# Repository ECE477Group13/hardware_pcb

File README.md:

# hardware_pcb
GitHub backup of PCB design files (Schematic and Board files)

here is a test change.

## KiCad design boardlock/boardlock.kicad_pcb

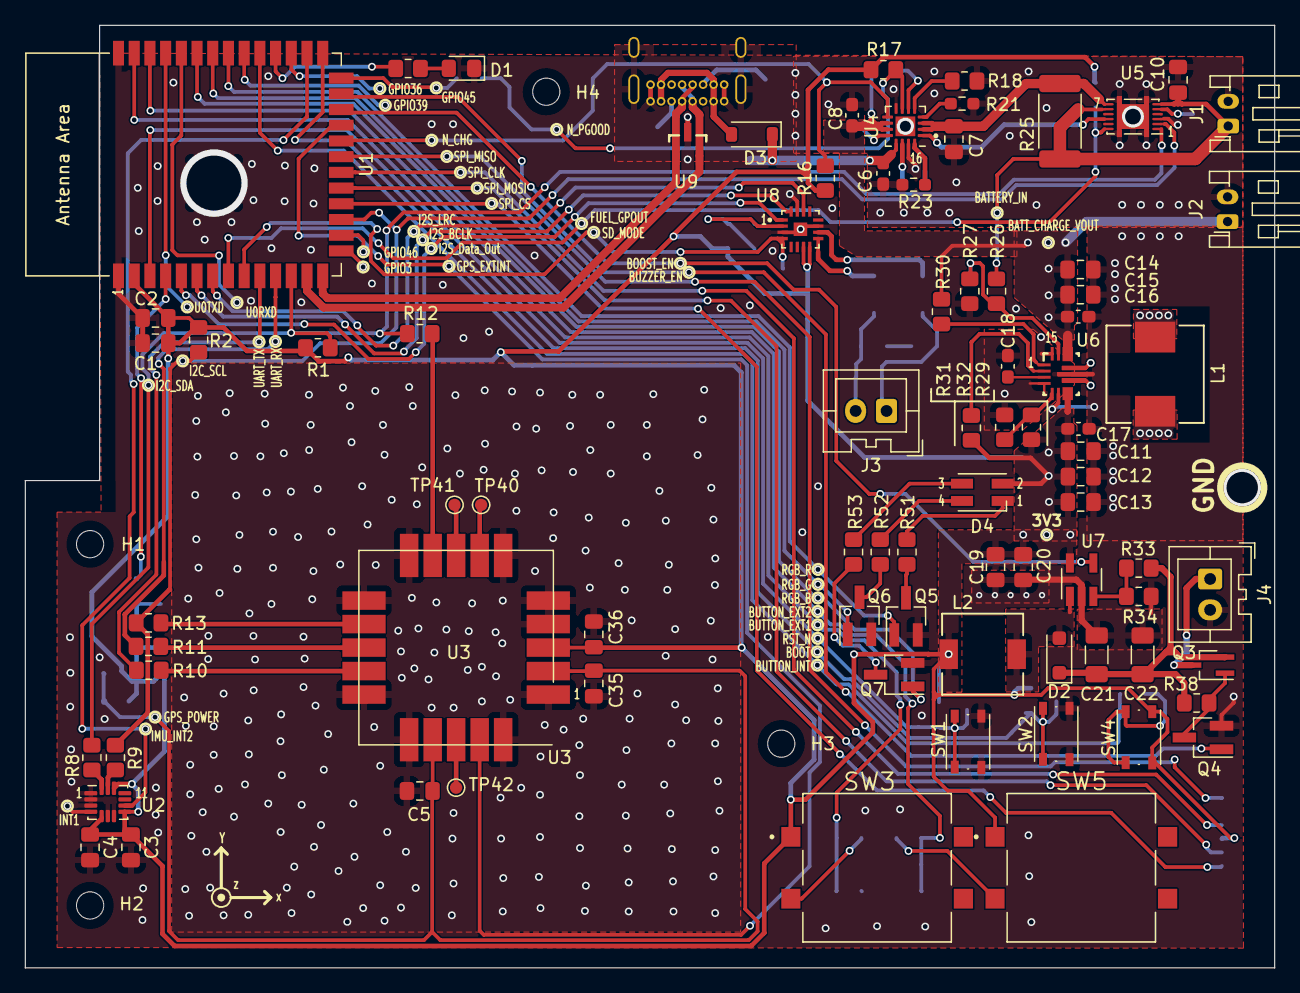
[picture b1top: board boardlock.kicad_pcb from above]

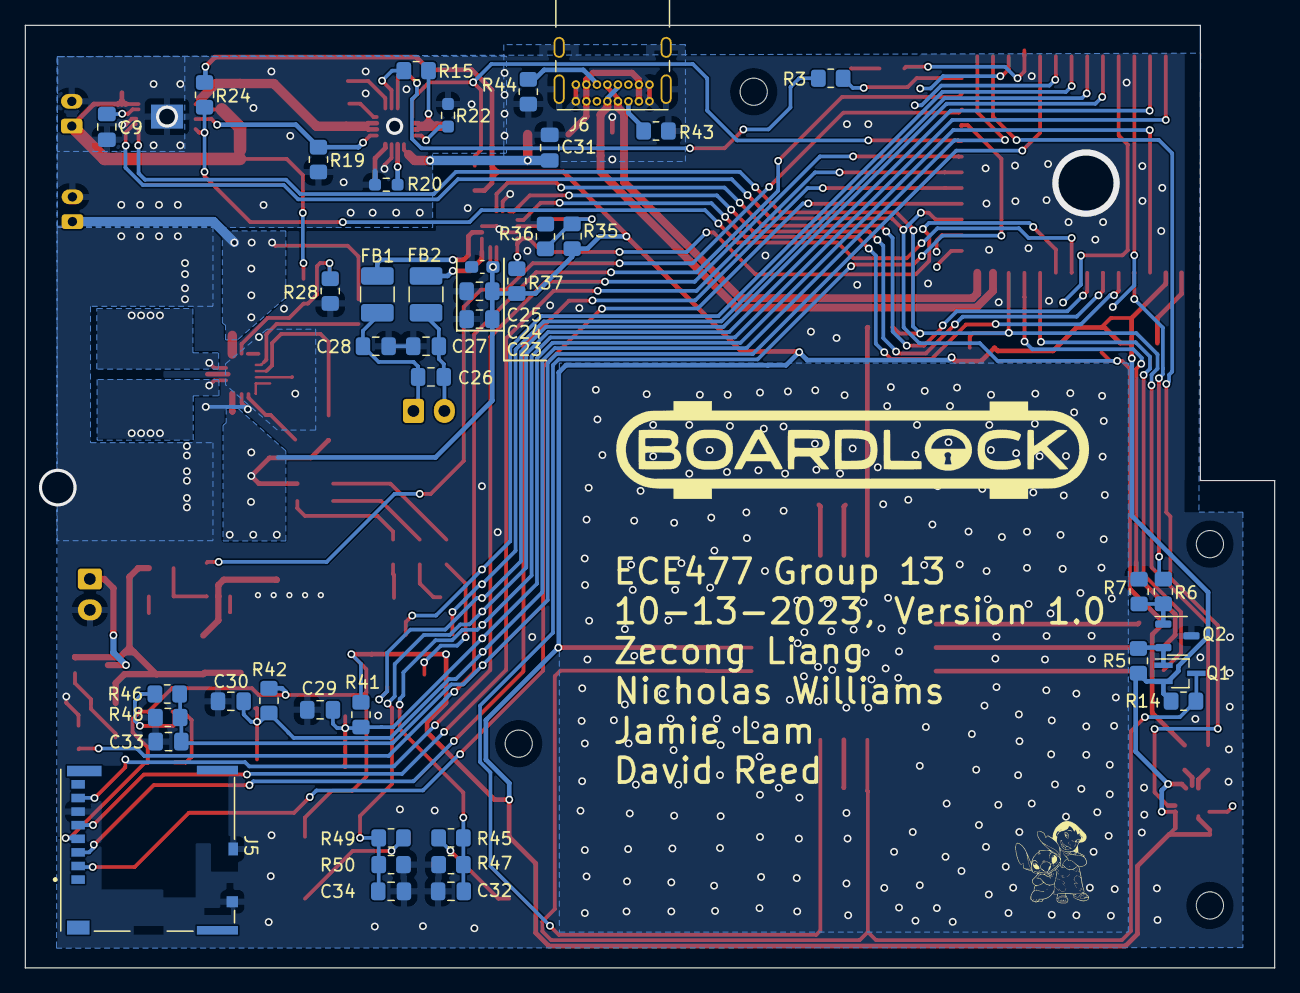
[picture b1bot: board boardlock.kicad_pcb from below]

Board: 2 copper layers, 101.0 x 76.2 mm, 129 parts (43 on the bottom side), 88 nets.

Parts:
C1, C7, C19, C20, C23, C24, C31: 10uF; C_0805_2012Metric_Pad1.18x1.45mm_HandSolder
C2, C29, C30, C32, C33, C34: 0.1uF; C_0805_2012Metric_Pad1.18x1.45mm_HandSolder
C3, C4: 100nF; C_0805_2012Metric_Pad1.18x1.45mm_HandSolder
C5, C35, C36: 1.0uF; C_0805_2012Metric_Pad1.18x1.45mm_HandSolder
C6: 1uF; C_0603_1608Metric_Pad1.08x0.95mm_HandSolder
C8, C16, C17: 10uF; C_0603_1608Metric_Pad1.08x0.95mm_HandSolder
C9: 0.47uF; C_0805_2012Metric_Pad1.18x1.45mm_HandSolder
C10: 1uF; C_0805_2012Metric_Pad1.18x1.45mm_HandSolder
C11, C12, C13, C14, C15: 22uF; C_0805_2012Metric_Pad1.18x1.45mm_HandSolder
C18: 100nF; C_0603_1608Metric_Pad1.08x0.95mm_HandSolder
C21, C22: 10uF; C_1206_3216Metric_Pad1.33x1.80mm_HandSolder
C25: 0.1uF; C_0603_1608Metric_Pad1.08x0.95mm_HandSolder
C26, C27, C28: 47n; C_0805_2012Metric_Pad1.18x1.45mm_HandSolder
D1: LED; LED_0805_2012Metric_Pad1.15x1.40mm_HandSolder
D2: PMEG2005EH; D_SOD-123F
D3: 1N5819HW1-7-F; D_SOD-123
D4: CLVBA-FKA-CC1F1L1BB7R3R3D; LED_Cree-PLCC4_3.2x2.8mm_CCW
FB1, FB2: 4.7uH; L_1210_3225Metric_Pad1.42x2.65mm_HandSolder
H1, H2, H3, H4: MountingHole; MountingHole_2.2mm_M2
J1, J2: Conn_01x02; JST_PH_S2B-PH-K_1x02_P2.00mm_Horizontal
J3, J4: Conn_01x02; JST_XA_B02B-XASK-1_1x02_P2.50mm_Vertical
J5: 5033981892; MOLEX_503398-1892
J6: USB_C_Receptacle_USB2.0; USB_C_Receptacle_GCT_USB4085
L1: 1.5uH; DR74
L2: 4.7uH; IND_EPCOS_B82462G4_EPC
Q1, Q3: BSS84PWH6327XTSA1; SOT-323_SC-70_Handsoldering
Q2: MMBT4401; SOT-23-3
Q4, Q5, Q6, Q7: DTC124X; SOT-23_Handsoldering
R1, R2, R16, R17, R43, R44: 5.1k; R_0805_2012Metric_Pad1.20x1.40mm_HandSolder
R3, R14: 0; R_0805_2012Metric_Pad1.20x1.40mm_HandSolder
R4, R5, R6, R7, R18, R38: R_US; R_0805_2012Metric_Pad1.20x1.40mm_HandSolder
R8, R9, R12, R13: 22; R_0805_2012Metric_Pad1.20x1.40mm_HandSolder
R10, R11: 470; R_0805_2012Metric_Pad1.20x1.40mm_HandSolder
R15: 1.2k; R_0805_2012Metric_Pad1.20x1.40mm_HandSolder
R19, R24, R30: 10k; R_0805_2012Metric_Pad1.20x1.40mm_HandSolder
R20: 47k; R_0603_1608Metric_Pad0.98x0.95mm_HandSolder
R21: 100k; R_0603_1608Metric_Pad0.98x0.95mm_HandSolder
R22, R23: 1.2k; R_0603_1608Metric_Pad0.98x0.95mm_HandSolder
R25: 10m; R_2512_6332Metric_Pad1.40x3.35mm_HandSolder
R26: 560k; R_0805_2012Metric_Pad1.20x1.40mm_HandSolder
R27, R28: 330k; R_0805_2012Metric_Pad1.20x1.40mm_HandSolder
R29: 470k; R_0805_2012Metric_Pad1.20x1.40mm_HandSolder
R31, R35, R36, R41, R42, R47, R48, R50: 100k; R_0805_2012Metric_Pad1.20x1.40mm_HandSolder
R32: 150k; R_0805_2012Metric_Pad1.20x1.40mm_HandSolder
R33: 1.05M; R_0805_2012Metric_Pad1.20x1.40mm_HandSolder
R34: 120k; R_0805_2012Metric_Pad1.20x1.40mm_HandSolder
R37: ?; R_0805_2012Metric_Pad1.20x1.40mm_HandSolder
R45, R46, R49: 1k; R_0805_2012Metric_Pad1.20x1.40mm_HandSolder
R51: 12; R_0805_2012Metric_Pad1.20x1.40mm_HandSolder
R52, R53: 5.6; R_0805_2012Metric_Pad1.20x1.40mm_HandSolder
SW1, SW2, SW4: SW_Push; SW_Push_1P1T_NO_Vertical_Wuerth_434133025816
SW3, SW5: TL3300DF160Q; SW_TL3300DF160Q
TP40: TIMEPULSE; TestPoint_Pad_D1.0mm
TP41: GPS_SAFE_N; TestPoint_Pad_D1.0mm
TP42: GPS_RESET_N; TestPoint_Pad_D1.0mm
U1: ESP32-S3-WROOM-1
U2: LSM6DSO32; LGA-14_3x2.5mm_P0.5mm_LayoutBorder3x4y
U3: SAM-M8Q; ublox_SAM-M8Q
U4: BQ24075RGT; VQFN-16-1EP_3x3mm_P0.5mm_EP1.6x1.6mm
U5: BQ27441DRZR-G1A; Texas_S-PDSO-N12
U6: TPS630701RNMR
U7: MCP1661; SOT-23-5_HandSoldering
U8: MAX98357AETE+T; QFN50P300X300X80-17N
U9: TPD2E2U06QDBZRQ1; DBZ0003A_N

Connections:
+3V3: C1.1, C2.1, C3.1, C4.1, C11.1, C12.1, C13.1, C17.1, C19.1, C20.1, C23.1, C24.1, C25.1, C36.1, D4.2 (A), J5.4 (VDD), L2.1, Q1.2 (S), R1.1, R2.1, R5.1, R14.1, R16.1, R17.1, R24.1, R29.1, R31.1, R35.1, R37.1, R41.1, R42.1, SW3.1, SW4.1, SW5.1, U1.2 (3V3), U2.5 (VDDIO), U2.8 (VDD), U2.12 (CS), U3.3 (V_BCKP), U6.7 (VOUT), U6.8 (VOUT), U7.5 (V_{IN}), U8.7 (VDD), U8.8 (VDD)
+12V: C21.1, C22.1, D2.1 (K), Q3.2 (S), R33.1, R38.1
+BATT: C7.1, R25.1, U4.2 (BAT), U4.3 (BAT), U5.7 (SRN)
/audio/BUZZER_POWER: J4.1, Q3.3 (D)
/audio/SPEAKER_NEG: C26.2, C27.1, FB2.1, J3.2
/audio/SPEAKER_POS: C26.1, C28.1, FB1.1, J3.1
/battery/ILIM: R22.1, U4.12 (ILIM)
/battery/ISET: R23.1, U4.16 (ISET)
/battery/N_Charge_EN: R21.1, U4.4 (~CE)
/battery/TIMER: R20.1, U4.14 (TMR)
/power/Buck_Boost_FB: R29.2, R32.1, U6.5 (FB)
/power/Buck_Boost_PG: R31.2, U6.2 (PG)
/power/PS_SYNC: R30.2, U6.1 (PS_SYNC)
/power/VAUX: C18.1, U6.3 (VAUX)
/ui/V_USB: D3.2 (A), J6.A4 (VBUS), J6.A9 (VBUS), J6.B4 (VBUS), J6.B9 (VBUS)
BATTERY_IN: C10.1, J1.1, R25.2, R26.1, U5.6 (BAT), U5.8 (SRP)
BATT_BUCK_BOOST_EN: R26.2, R27.1, R28.1, U6.14 (EN)
BATT_CHARGE_EN1: R15.2, U4.6 (EN1)
BATT_CHARGE_EN2: R18.1, U4.5 (EN2)
BATT_CHARGE_VOUT: C8.1, C14.1, C15.1, C16.1, J2.1, R15.1, R30.1, U4.10 (OUT), U4.11 (OUT), U6.12 (VIN), U6.13 (VIN)
GAIN_SLOT: R35.2, R36.1, U8.2 (GAIN_SLOT)
GND: C1.2, C2.2, C3.2, C4.2, C5.2, C6.2, C7.2, C8.2, C9.2, C10.2, C11.2, C12.2, C13.2, C14.2, C15.2, C16.2, C17.2, C18.2, C19.2, C20.2, C21.2, C22.2, C23.2, C24.2, C25.2, C27.2, C28.2, C29.2, C30.2, C31.2, C32.2, C33.2, C34.2, C35.2, C36.2, D1.1 (K), J1.2, J2.2, J4.2, J5.6 (VSS), J5.9 (DET), J5.10 (SHIELD), J6.A1 (GND), J6.A12 (GND), J6.B1 (GND), J6.B12 (GND), J6.S1 (SHIELD), Q2.3 (E), Q4.2 (E), Q5.2 (E), Q6.2 (E), Q7.2 (E), R7.2, R18.2, R19.2, R20.2, R21.2, R22.2, R23.2, R27.2, R28.2, R32.2, R34.2, R36.2, R43.2, R44.1, R47.1, R48.1, R50.1, SW1.1, SW2.1, U1.1 (GND), U1.40 (GND), U1.41 (GND), U2.1 (SDO/SA0), U2.2 (SDX), U2.3 (SCX), U2.6 (GND), U2.7 (GND), U3.1 (GND), U3.4 (GND), U3.5 (GND), U3.6 (GND), U3.10 (GND), U3.11 (GND), U3.15 (GND), U3.16 (GND), U3.20 (GND), U4.8 (VSS), U4.15 (SYSOFF), U4.17 (VSS), U5.3 (V_{SS}), U5.13 (PAD), U6.4 (GND), U6.6 (FB2), U6.10 (PGND), U6.15 (VSEL), U7.2 (GND), U8.3 (GND), U8.11 (GND), U8.15 (GND), U8.17 (EP), U9.3 (GND)
GPS_POWER: C5.1, C35.1, Q1.3 (D), R14.2, U3.2 (VCC_IO), U3.17 (VCC)
M_AUDIO_SD_MODE: R37.2, U1.9 (GPIO16/U0CTS/ADC2_CH5/XTAL_32K_N), U8.4 (SD_MODE)
M_BATT_CHARGE_N_CHG: R16.2, U1.22 (GPIO14/TOUCH14/ADC2_CH3/FSPIWP/FSPIDQS/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), U4.9 (~CHG)
M_BATT_CHARGE_N_PGOOD: R3.2, R17.2, U4.7 (~PGOOD)
M_BOOST_EN: U1.24 (GPIO47/SPICLK_P/SUBSPICLK_P_DIFF), U7.4 (EN)
M_BOOT: C30.1, R42.2, SW2.2, U1.27 (GPIO0/BOOT)
M_BUTTON_EXT1: C32.1, R45.2, R47.2, U1.39 (GPIO1/TOUCH1/ADC1_CH0)
M_BUTTON_EXT2: C34.1, R49.2, R50.2, U1.38 (GPIO2/TOUCH2/ADC1_CH1)
M_BUTTON_INT: C33.1, R46.2, R48.2, U1.31 (GPIO38/FSPIWP/SUBSPIWP)
M_BUZZER_EN: Q4.1 (B), U1.25 (GPIO48/SPICLK_N/SUBSPICLK_N_DIFF)
M_FUEL_GPOUT: R24.2, U1.8 (GPIO15/U0RTS/ADC2_CH4/XTAL_32K_P), U5.12 (GPOUT)
M_GPS_EXTINT: U1.23 (GPIO21), U3.19 (EXTINT)
M_GPS_POWER: R6.1, U1.4 (GPIO4/TOUCH4/ADC1_CH3)
M_HEARTBEAT: R4.1, U1.30 (SPIDQS/GPIO37/FSPIQ/SUBSPIQ)
M_I2C_SCL: R2.2, R9.1, R13.1, U1.17 (GPIO9/TOUCH9/ADC1_CH8/FSPIHD/SUBSPIHD), U5.2 (SCL)
M_I2C_SDA: R1.2, R8.1, R12.1, U1.12 (GPIO8/TOUCH8/ADC1_CH7/SUBSPICS1), U5.1 (SDA)
M_I2S_BCLK: U1.6 (GPIO6/TOUCH6/ADC1_CH5), U8.16 (BCLK)
M_I2S_Data_Out: U1.5 (GPIO5/TOUCH5/ADC1_CH4), U8.1 (DIN)
M_I2S_LRC: U1.7 (GPIO7/TOUCH7/ADC1_CH6), U8.14 (LRCLK)
M_IMU_INT2: U1.28 (SPIIO6/GPIO35/FSPID/SUBSPID), U2.9 (INT2)
M_RGB_B: Q7.1 (B), U1.35 (MTMS/GPIO42)
M_RGB_G: Q6.1 (B), U1.34 (MTDI/GPIO41/CLK_OUT1)
M_RGB_R: Q5.1 (B), U1.33 (MTDO/GPIO40/CLK_OUT2)
M_RST_N: C29.1, R41.2, SW1.2, U1.3 (EN)
M_SPI_CLK: J5.5 (CLK), U1.20 (GPIO12/TOUCH12/ADC2_CH1/FSPICLK/FSPIIO6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)
M_SPI_CS: J5.2 (DAT3/CD), U1.18 (GPIO10/TOUCH10/ADC1_CH9/FSPICS0/FSPIIO4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)
M_SPI_MISO: J5.7 (DAT0), U1.21 (GPIO13/TOUCH13/ADC2_CH2/FSPIQ/FSPIIO7/S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)
M_SPI_MOSI: J5.3 (CMD), U1.19 (GPIO11/TOUCH11/ADC2_CH0/FSPID/FSPIIO5/S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)
M_UART_RX: R11.1, U1.11 (GPIO18/U1RXD/ADC2_CH7/CLK_OUT3)
M_UART_TX: R10.1, U1.10 (GPIO17/U1TXD/ADC2_CH6)
unnamed: D1.2 (A), R4.2
unnamed: D2.2 (A), L2.2, U7.1 (SW)
unnamed: D4.3 (BK), R53.1
unnamed: D4.4 (GK), R52.1
unnamed: D4.1 (RK), R51.1
unnamed: J6.A5 (CC1), R43.1
unnamed: J6.B5 (CC2), R44.2
unnamed: Q1.1 (G), Q2.2 (C), R5.2
unnamed: Q2.1 (B), R6.2, R7.1
unnamed: Q3.1 (G), Q4.3 (C), R38.2
unnamed: Q5.3 (C), R51.2
unnamed: Q6.3 (C), R52.2
unnamed: Q7.3 (C), R53.2
unnamed: R45.1, SW3.3
unnamed: R46.1, SW4.2
unnamed: R49.1, SW5.3
unnamed: R3.1, U1.26 (GPIO45)
unnamed: R9.2, U2.13 (SCL)
unnamed: R8.2, U2.14 (SDA)
unnamed: R10.2, U3.14 (RXD)
unnamed: R13.2, U3.12 (SCL)
unnamed: R12.2, U3.9 (SDA)
unnamed: TP40.1, U3.7 (TIMEPULSE)
unnamed: R11.2, U3.13 (TXD)
unnamed: TP42.1, U3.18 (~RESET)
unnamed: TP41.1, U3.8 (~SAFEBOOT)
unnamed: C9.1, U5.5 (V_{DD})
unnamed: L1.1, U6.11 (L1)
unnamed: L1.2, U6.9 (L2)
unnamed: R33.2, R34.1, U7.3 (V_{FB})
unnamed: FB1.2, U8.10 (OUTN)
unnamed: FB2.2, U8.9 (OUTP)
TS_RESISTOR: R19.1, U4.1 (TS), U5.10 (BIN)
USB_D+: J6.A6 (D+), J6.B6 (D+), U1.14 (GPIO20/U1CTS/ADC2_CH9/CLK_OUT1/USB_D+), U9.1 (IO1)
USB_D-: J6.A7 (D-), J6.B7 (D-), U1.13 (GPIO19/U1RTS/ADC2_CH8/CLK_OUT2/USB_D-), U9.2 (IO2)
VBUS: C6.1, C31.1, D3.1 (K), U4.13 (IN)

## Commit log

2023-09-05 BoardLock KiCAD file init
2023-09-05 created pages for sensors, audio, and power
2023-09-05 Started adding IMU and GPS circuits
2023-09-05 updated GPS circuit
2023-09-05 updates power control circuit
2023-09-05 updated comments
2023-09-06 small GPS changes and added .gitignore
2023-09-06 last update before giving to David
2023-09-06 rename sensors.sch
2023-09-06 fixed some weird file naming issue
2023-09-06 removed boarlock_back backups
2023-09-06 restored custom library files
2023-09-06 updated audio power
2023-09-06 Started adding audio schematics
2023-09-07 GPS I2C version
2023-09-12 Installed library for ESP32-S3
2023-09-12 Added ESP32 library and SCH edits
2023-09-12 ESP32 connection edits
2023-09-13 Deleted an error
2023-09-13 deleted UART GPS
2023-09-14 Added power library and fixed labels
2023-09-14 updated libraries and edited symbols
2023-09-17 added buck boost topology
2023-09-18 Started adding topology for batt charger
2023-09-19 edited battery management
2023-09-19 sensor wire modifications
2023-09-19 added SPI and SD connections
2023-09-20 modifications?
2023-09-20 NPN?
2023-09-23 fake commit
2023-09-23 beep boop
2023-09-25 net label updates
2023-09-25 Zecong edits
2023-09-26 More zecong edits
2023-09-26 gps updates and protocol testpoints
2023-09-26 finishing touches
2023-09-26 imu check
2023-09-26 name change
2023-09-27 saving
2023-09-27 Added 1 USB protection diode
2023-09-27 prepping merge
2023-09-27 renaming testpoints to misc
2023-09-27 RBG, boot, reset
2023-09-27 buttons and stuff
2023-09-27 lab updates
2023-09-28 No tented via setting
2023-10-01 not sure what I changed
2023-10-01 added footprints and an LPF to audio
2023-10-01 continuing to add footprints
2023-10-01 note about GPOUT
2023-10-01 allocated pins
2023-10-02 footprint updates
2023-10-03 more footprint selection
2023-10-04 added buzzer power circuit
2023-10-04 footprint work
2023-10-04 added inductor footprints
2023-10-04 footprints finished for now
2023-10-04 Nick PCB edits
2023-10-05 SOmething
2023-10-05 pad extensions for GPS and IMU, and IMU footprint added
2023-10-05 nevermind still need to extend IMU
2023-10-06 changed IMU footprint to extended pads
2023-10-06 PCB: added keep out areas on edge
2023-10-06 Repositioned USB C port
2023-10-07 pulldowns on SWs and re-orienting pcb
2023-10-07 Small cleanup
2023-10-09 USB traces
2023-10-09 changed sides
2023-10-09 correcting old schematic and footprints
2023-10-09 pcb issues hopefully fixed
2023-10-09 pcb work
2023-10-09 more pcb stuff
2023-10-10 PCB: completed fuel gauge
2023-10-10 buck-boost WIP
2023-10-10 much buck-boost progress
2023-10-10 savinig before moving USB-C
2023-10-10 started on boost converter
2023-10-10 gps pcb stuff
2023-10-10 updating gps caps
2023-10-10 led changes
2023-10-10 step
2023-10-10 step 2
2023-10-11 buck-boost complete
2023-10-11 boost conveter complete
2023-10-11 starting on audio amp
2023-10-11 added LED to lock location
2023-10-11 completed audio amp
2023-10-11 added LED connections
2023-10-11 lots of wires
2023-10-11 more pcb
2023-10-11 starting I2S on PCB
2023-10-11 move ext butt popcorn
2023-10-11 connecting M_signals
2023-10-11 trying to figure out GPS power
2023-10-11 placed drill origin
2023-10-11 updated 3D model
2023-10-12 power connections
2023-10-12 silkscreen front
2023-10-12 silkscreen back
2023-10-12 starting testpoint elimination
2023-10-12 testpoint elimination
2023-10-12 making 3.3 bigger and deleting testpoints
2023-10-12 some changes
2023-10-12 Nick adding Stitch and DRC fixes
2023-10-12 button and power fixes
2023-10-12 added vias to not get flamed
2023-10-12 zecong adds a single via
2023-10-13 adding kicad_prl
2023-10-13 added some GND vias
2023-10-13 view settings change
2023-10-13 another via got deleted
2023-10-13 spelling error
2023-10-13 small edits
2023-10-13 gerber files
2023-10-14 added new drill file
2023-10-14 added another GND stitching via
2023-10-14 replaced TVS footprint and rerouted USB
2023-10-14 new GERBER generation
2023-10-14 new TVS diode symbol
2023-10-15 saving some change idk
2023-10-15 Added 3D models, moved HB res
2023-10-15 rmvbtemp folder
2023-10-17 add new via graphics
2023-10-17 moved main GND via
2023-10-18 reducing USB data line separation
2023-10-18 fixed silkscreen on c26 c27
2023-10-18 renamed holes
2023-10-18 via fixes
2023-10-18 micro pad extensions
2023-10-18 usb line changes
2023-10-18 the order
2023-10-18 created pdf drawings of gerbers
2023-12-09 Manufacturing and debugging mods in SCH
